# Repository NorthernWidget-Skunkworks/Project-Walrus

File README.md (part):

# The Walrus: A Pressure and Temperature Sensor for Water-Level and Barometric Measurements

***Our Walrus sensor, like this Walrus pup, is equally at home on land or in the water.*** *[Photo by Max Smith](https://commons.wikimedia.org/wiki/File:Walrus_-_Kamogawa_Seaworld_-_pup_-1.jpg)*

## Overview

The **Walrus** is an open-source sensor that measures temperature and pressure. It may be used in the air as a barometer or underwater as part of a system -- combined with barometric compensation -- to obtain changes in water level.

***Hard-mount variant of the Walrus.*** Major components are labeled. The pads to attach the watertight plug for the cable (i.e. the "HardMount"), on left, are currently unpopulated. These may be used for this kind of connector, or may have wires soldered directly to them before being embedded in an epoxy or other potting (i.e., waterproofing and encapsulating) compound.

### Technical specifications

#### Size

Dimensions: 42.0 x 12.7 cm

>> ADD MASS once I get access to a lab balance again <<

#### Operating ranges

**Power**
* Input Voltage: 3.3 to 5.5 V DC
* Logic Voltage: 0 to Vcc (Will operate at same logic level as input power supply)

**Sensors**
* Temperature: -40 to +85 C
* Pressure, typical: 0 to 2 atm (i.e. barometer to 10 m water depth)
* Pressure, maximum, untested: 0 to 30 atm (i.e. barometer to 290 m water depth)
* Cable length: 3 m (I2C) or 1000 m (RS-485).

The pressure operating range depends on the sensor element used. The [**MS5803-02BA**](https://www.te.com/commerce/DocumentDelivery/DDEController?Action=srchrtrv&DocNm=MS5803-02BA&DocType=Data+Sheet&DocLang=English) is the standard model that we use for pressure measurements of up to 10 m

The pressure transducer contains an internal temperature sensor, and a secondary (and more accurate) external temperature sensor is also mounted on the *Walrus*. This external sensor is the [MCP9808](http://www.microchip.com/mymicrochip/filehandler.aspx?ddocname=en556196) in an 8-MSOP package. This sensor has a range of -40 to 125 C.

RS-485 communications allow for a signal to be transmitted over long distances, but require a device that can decode this signal, such as our [Project-Longbow](https://github.com/NorthernWidget-Skunkworks/Project-Longbow).

#### Resolution

Pressure: +/- 1 mm water (0.1 mbar)
Temperature sensor within pressure transducer (typical): +/- 2.0 C
External temperature sensor (typical): +/- 0.5 C

## Circuit board and assembly

The Walrus comes in two forms:
* [Large form factor, through-hole mount](https://github.com/NorthernWidget-Skunkworks/Project-TPDH-Walrus/tree/master/Hardware_LargePTH): This is the legacy board with support for I2C and full-duplex RS-485 communication
* [Smaller form factor, solder pads for wires or a waterproof plug](https://github.com/NorthernWidget-Skunkworks/Project-TPDH-Walrus/tree/master/Hardware_HardMount): This current version makes better use of board space and utilizes a half-duplex RS-485 bus in addition to an I2C bus.

### Files

The files for production are located in folders starting with the word "Hardware". These folders contain:

* "\*.brd" and "\*.sch" files. These are the circuit board and its schematic for use with the EAGLE CAD software, which you can download for free: https://www.autodesk.com/products/eagle/free-download
* A "\*.csv" file that contains the "BoM" -- the bill of materials. This lists all required parts to construct the board
* A ZIP archive containing a set of "Gerber" files. These are the files that machines use to create a circuit board and a stencil to help you to apply solder paste (see below)

### Circuit board specifications

* 2-layer copper
* Minimum trace width: 0.2 mm
* Single-sided
* Surface mount components

All Walrus boards are **single-sided** and use only **surface-mount components** for rapid fabrication using standard equipment.

### Producing circuit boards

We strongly recommend that circuit boards be printed by a reputible manufacturer. Many such industries exist in China, India, and developing or developed countries.

### Populating circuit boards

Before you can start to populate the circuit board, meaning adding components to it, you will need solder paste and a stencil. If you have access to a laser cutter, you can create your own stencil (https://learn.adafruit.com/smt-manufacturing/laser-cut-stencils). If you do not, the company that prints the circuit boards should be able to provide one. If all else fails, you can try to cut out a stencil with a small knife, or use a solder-paste syringe, though both of these methods can lead to difficulties (such as bridged connections). Additional information on how to stencil can be found here: https://www.sparkfun.com/tutorials/58.

To help you in using the stencil, we provide STL files for 3D-printable plates in each of the hardware directories. These plates hold the board in place and provide a level surface on which to use the stencil.

>> ADD PLATE FOR HARDMOUNT <<

After this, you can use a tweezers and steady hands, or a pick-and-place machine, to gently place each component over the right pads, and in the right orientation. Do not worry if they are slightly misaligned; the surface tension of the solderi, once it is melted, will help to rotate the components into place.

### Reflowing circuit boards

"Reflowing" is the process of heating solder until it flows and attaches to components. A basic introduction is here: https://learn.sparkfun.com/tutorials/electronics-assembly/reflow

There are four major ways to reflow:
1. Using a professional oven (see link above)
2. With a customized toaster oven: See https://www.sparkfun.com/tutorials/60, and a basic internet search will show you many, many other ideas
3. You can also use a simple electrical skillet -- the kind that you might use to make some food. https://www.sparkfun.com/tutorials/59
4. Using a hot-air rework station; this is a bit time-intensive, but lets you control the heat, and I often use it for small boards. https://learn.sparkfun.com/tutorials/how-to-use-a-hot-air-rework-station/all

After reflowing, you may need to clean up jumped connections using **solder wick**.

### Debugging circuit boards

After reflow is complete, check if everything worked. Do you have any jumped connections? Any remaining solder paste that hasn't been reflowed? This can be the trickiest part, and one for which access to a multimeter is essential. An oscilloscope and a digital logical analyzer can help too. Debugging electronic circuit boards is a process that requires significant skill and practice, so be sure that you can work with someone with some expertise. I would suggest an electrical engineering student or professor at a local university.

## Wiring and pinout

"Pin" is the name of the pin as labeled on the board. "Wire" is the color of the [Alpha Wire 5004C cable](https://www.digikey.com/product-detail/en/alpha-wire/5004C-SL001/5004CSL001-ND/484976) that we use; you may use something different based on what manufacturers exist where you are; that's okay, just record the color convention! (We sometimes use another cable in which we use a white wire for SDA and a green wire for SCL, but have found that Alpha Wire brand works best.)

>> Add image of cable ends (optional) and find how to integrate with housing section; cabling is a distinct topic, but the step of attaching the cable lies within the housing-construction step <<

### HardMount with plug

Here we assume that you are using standard Alpha Wire cables with waterproof attachments, available in [3-meter](https://www.digikey.com/en/products/detail/alpha-wire/AR0400101-SL357/6555492) and [1-meter](https://www.digikey.com/en/products/detail/alpha-wire/AR0400101-SL356/6555491) lengths; the 3-meter length is our standard because this is the longest that it can be and still communicate reliably via I2C. Because of the wire insulation colors available for these cables and the locations of their attachment points to the [4-pin "HardMount" plug](https://www.digikey.com/product-detail/en/te-connectivity-amp-connectors/1838893-2/A97650-ND/1764165) ([3D model](https://www.traceparts.com/en/product/allied-electronics-automation-m12-panel-mnt-male-4-way?CatalogPath=TRACEPARTS%3ATP09002002001004&Product=10-12012018-106023&PartNumber=1838893-2)), **our HardMount devices do NOT match standard wire-color definitions (or any kind of standard)**. Wire-color definitions are:

| **Color** | **Connection**        |
|-----------|-----------------------|
| Brown     | V+ (3.3-5.5 V)        |
| White     | GND                   |
| Black     | SIG1: SDA or RS-485 A |
| Blue      | SIG2: SCL or RS-485 B |

### Large-form-factor/PTH design: standard wiring suggestion

*These are our more standard wire-color suggestions*

| **Color** | **Connection**                   |
|-----------|----------------------------------|
| Red       | V+ (3.3-5.5 V)                   |
| Black     | GND                              |
| Brown     | SIG1: SDA or RS-485 A (RX+, TX+) |
| Orange    | SIG2: SCL or RS-485 B (RX-, TX-) |

If you attach your own wire, pins on the Walrus are as follows, looking at the top side with the screw hole away from you:
* Top left: SIG1: SDA for I2C; A (+) for RS-485
* Top right: SIG 2: SCL for I2C; B (-) for RS-485
* Bottom left: VCC (3.3V to 5.5V)
* Bottom right: GND

## Upload the firmware

### Downloading and installing the Arduino IDE

Go to https://www.arduino.cc/en/main/software. Choose the proper IDE version for your computer. For Windows, we suggest the non-app version to have more control over Arduino; this might change in the future. You will have to add custom libraries, so the web version will not work (at least, as of the time of writing). Download and install the Arduino IDE. Open it to begin the next steps.

### AVR ISP

To install firmware on the Walrus, you use the [2x3-pin ICSP (also called ISP) header](https://www.digikey.com/product-detail/en/3m/929665-09-03-I/3M156313-06-ND/681796) with a special device called an "in-circuit system programmer" (or just "in-system programmer; yup, that's what the acronym stands for).

Many devices exist to upload firmware, including:
* The official [AVR ISP mkII](http://ww1.microchip.com/downloads/en/DeviceDoc/Atmel-42093-AVR-ISP-mkII_UserGuide.pdf) (no longer produced but available used)
* Using an [Arduino as an ISP](https://www.arduino.cc/en/tutorial/arduinoISP)
* The versatile [Olimex AVR-ISP-MK2](https://www.olimex.com/Products/AVR/Programmers/AVR-ISP-MK2/open-source-hardware)
* The [Adafruit USBtinyISP](https://www.adafruit.com/product/46)

***Note: Be sure to download and/or update drivers for your ISP.***

### Uploading the firmware

Using an AVR ISP, upload the proper firmware programs from the ["Firmware" directory](Firmware) in this repository using the Arduino software:
* Large form factor PTH board
  * I2C mode: No firmware required, but fuses must be set (see instructions, below)
  * RS-485 mode: [Longbow_2BA_0x6B](Firmware/Longbow_2BA_0x6B) (This firmware is for the 02BA; you will need to switch these with other coefficients, available in the commented and uncommented lines of /Firmware/Walrus_I2C_5BA, to modify this for a different transducer pressure range.)
* Small form factor hard-mount board
  * I2C mode: Set the fuses (see instructions below) and then upload [Walrus_I2C_5BA](/Firmware/Walrus_I2C_5BA/) (This firmware is for the 05BA; there are lines in this code to comment and uncomment to modify it for other versions of the Walrus.)
  * RS-485 mode: [Longbow_2BA_0x6B_HalfDuplex](Firmware/Longbow_2BA_0x6B_HalfDuplex) (This firmware is for the 02BA; you will need to switch these with other coefficients, available in the commented and uncommented lines of /Firmware/Walrus_I2C_5BA, to modify this for a different transducer pressure range.)

>> @bschulz1701: could you provide a link to the repo (is it TPDH lib) for "  * I2C mode: No firmware required. Library communicates directly with sensors via their built-in I2C addresses."

**Instructions:**

1. Open the Arduino IDE.
2. Follow [these instructions](https://github.com/SpenceKonde/ATTinyCore/blob/master/Installation.md) to install the [ATTinyCore board definitions](https://github.com/SpenceKonde/ATTinyCore)
3. Select [ATTiny1634](https://github.com/SpenceKonde/ATTinyCore/blob/master/avr/extras/ATtiny_1634.md) **(No bootloader)**
4. Plug your ISP of choice into your computer (via a USB cable) and onto the 6-pin header. There are two ways to place it on; the header is aligned such that the ribbon cable should be facing away from the board while programming. If this fails without being able to upload, try flipping the header around. This should both power the board and provide communications.
5. Go to Tools --> Programmer and select the appropriate programmer based on what you are using.
6. Go to Tools --> Burn Bootloader. Yes, we know that you just selected "ATTiny1634 (No bootloader)", but this step sets the fuses, which configure their internal oscillator and brown-out detection.
7. Unless you are configuring a large-form-factor Walrus in I2C mode (in which case you are now done), open the appropriate firmware (linked above). Then go to Sketch --> Upload Using Programmer. After several seconds, you learn whether you succeeded or failed. Hopefully it worked!

***Uploading using the in-system programmer.***

***Important note for Linux users:*** You must supply permissions to the Arduino IDE for it to be able to use the ICSP, or you will have to run it using `sudo`. The former option is better; the latter is easier in the moment.

## Register map and firmware internals

The Walrus firmware runs on an ATMega microcontroller and exposes an I2C register map to the host logger. The default I2C address is `0x4D`.

Two layouts exist: the **current firmware** (deployed) and the **proposed** layout under [NW-Device-Specification](https://github.com/NorthernWidget/NW-Device-Specification) Schema 1, which the firmware will be updated to implement.

### Current register map (deployed firmware)

26-byte array. Identity fields (MODEL, GROUPID, INDID, FIRMWAREID) mixed into sensor data. Status ready flag is bit 7.

```
0x00        CTRL/Status   bit 7=ready; bits 1:0=update rate selector (0–3)
0x01        —             unused
0x02–0x05   Pressure      int32, µBar (library: val/1000.0 → mBar)
0x06–0x09   Temp ext      int32, 1/10000 °C (MCP9808 external sensor)
0x0A–0x0D   Temp MS5803   int32, 1/10000 °C (MS5803 internal sensor)
0x0E–0x0F   MODEL         uint16 (0x5702)
0x10–0x11   —             gap (nothing loaded)
0x12–0x13   GROUPID       uint16
0x14–0x15   INDID         uint16
0x16–0x17   FIRMWAREID    uint16 (0x0001)
```

### Proposed register map (NW-Device-Specification Schema 1)

Two 32-byte pages. Identity moves entirely to Page 0 (EEPROM). Sensor data in Page 1 (SRAM). No calibration page (MS5803 coefficients are read from its internal PROM at startup).

**Page 0 (0x00–0x1F) — Identity (EEPROM)**

```
Block 0 (0x00–0x07)   Core identity
  0x00        0x01              Schema (NW-Device-Specification v1)
  0x01–0x06   'W','a','l','r','u','s'   Device name (ASCII)
  0x07        0x00              Null padding

Block 1 (0x08–0x0F)   Version
  0x08        HW major
  0x09        HW minor
  0x0A        FW patch          (NW combined-repo convention)
  0x0B–0x0D   0x00,0x00,0x00    Unused (combined repo)
  0x0E–0x0F   0x00,0x00         Reserved

Block 2 (0x10–0x17)   Serial number
  0x10–0x11   0x5702            Board type ('W'=0x57, revision index 2; matches MODEL)
  0x12–0x13   [manufacture]     Group ID
  0x14–0x15   [manufacture]     Unique ID
  0x16–0x17   0x00,0x00         FirmwareID (legacy, reserved)

Block 3 (0x18–0x1F)   Integrity + administration
  0x18–0x1C   0x00 ×5           Reserved
  0x1D        0x00              Magic byte (reserved; purpose TBD)
  0x1E        [computed]        CRC-8 of bytes 0x00–0x1D
  0x1F        0x4D              I2C address (writable; 0xFF = use default)
```

**Page 1 (0x20–0x3F) — Sensor data (SRAM)**

```
Block 0 (0x20–0x27)   MS5803 — pressure + temperature
  0x20        Status       bit 0=ready, bit 1=MS5803 fault, bit 2=ext temp fault
  0x21–0x24   Pressure     int32, µBar, little-endian
  0x25–0x26   Temp MS5803  int16, 0.01 °C, little-endian
  0x27        Reserved

Block 1 (0x28–0x2F)   External temperature sensor (MCP9808)
  0x28–0x29   Temp ext     int16, 0.01 °C, little-endian
  0x2A–0x2F   Reserved

Block 2–3 (0x30–0x3F)   Reserved
```

### Open items before firmware update

Three issues must be resolved before implementing Schema 1:

1. **Status bit:** Current firmware uses bit 7 as the ready flag; Schema 1 uses bit 0. Library `newData()` must be updated to match.
2. **Temperature precision:** Current firmware stores 1/10000 °C (int32, 4 bytes); proposed Schema 1 uses 0.01 °C (int16, 2 bytes). Sensor accuracy (MCP9808 ±0.0625 °C, MS5803 ±1 °C) is well within 0.01 °C resolution.
3. **Pressure units:** Current firmware uses µBar; Haar Schema 1 proposes 0.01 hPa (1 µBar = 0.001 hPa — different units). Resolve unit choice in [NW-Device-Specification](https://github.com/NorthernWidget/NW-Device-Specification) before updating either firmware.

## Housing

### Large-form-factor PTH design

***Walrus v0.0.0 PTH and its housing.*** *Left: 3D-printed top of the housing; the slits are to prevent large material from hitting the sensor. Center: the bottom of the housing. Self-tapping holes are to screw the board onto this housing. The cable entering the housing through a tightly-fitting hole on the "south" side of the image has not yet been stripped to expose the ends of the individual wires. A different variant of the housing is longer to allow the user to strip more of the cable if desired while maintaining the cable jacketing in contact with the hole. Top right: Walrus v0.0.0. This fully-functional initial version is significantly larger than the current unit. Note the pressure transducer (white circle) at top left, and the fact that this has pins and hardware for a full-duplex RS-485 connection. Bottom right: U.S. penny for scale; 19.05 mm (0.75 inch) diameter.*

### HardMount design

***Render of the enclosure design.*** *The epoxy encapsulation tray sits within a wider cylinder containing a screen designed to keep sediment out. Design still in progress (19 June 2020).*

### How to build

#### Materials and components required

##### All models

* 3D printer filament: ABS suggested
* Two-part epoxy: [3M DP270 Clear](https://multimedia.3m.com/mws/media/66773O/3mtm-scotch-weldtm-epoxy-potting-compound-adhesive-dp270.pdf); can be purchased from [McMaster-Carr](https://www.mcmaster.com/7467A274)
* Conformal coating to help protect components during epoxy encapsulation. We suggest [MG 419D](https://www.mgchemicals.com/products/conformal-coatings/acrylic-conformal-coating-419d) ([Digi-Key purchase link](https://www.digikey.com/product-detail/en/mg-chemicals/419D-55ML/473-1388-ND)). If you prefer a silicone conformal coat, we suggest [MG 422C](https://www.mgchemicals.com/products/conformal-coatings/422c-silicone-conformal-coating), though we recommend this instead for an external (rather than internal, as this will be), flexible coat.

##### HardMount with Plug

* [4-pin "HardMount" plug](https://www.digikey.com/product-detail/en/te-connectivity-amp-connectors/1838893-2/A97650-ND/1764165) ([3D model](https://www.traceparts.com/en/product/allied-electronics-automation-m12-panel-mnt-male-4-way?CatalogPath=TRACEPARTS%3ATP09002002001004&Product=10-12012018-106023&PartNumber=1838893-2))
* HardMount cable: **Alpha Wire AR0400105-SL357** (-40 PVC jacket)
  * [Alpha Wire page](http://www.Alpha Wire.com/en/Products/Connectivity/AlphaConnect/Cordsets/AR0400105)
  * [Example from DigiKey](https://www.digikey.com/product-detail/en/alpha-wire/AR0400105-SL357/AR0400105SL357-ND/6555497)
  * Comes in a [variety of lengths from 0.6 to 20 meters](http://www.Alpha Wire.com/en/Products/Connectivity/AlphaConnect/Cordsets/AR0400105) ([Digi-Key search results](https://www.digikey.com/products/en/cable-assemblies/circular-cable-assemblies/448?FV=2331%7C312745%2C2344%7C346572%2C2350%7C349292%2C2380%7C203167%2C-8%7C448%2C2345%7C1%2C2352%7C387800&quantity=0&ColumnSort=77&page=1&stock=1&rohs=1&nstock=1&k=M12+Alpha+Wire&pageSize=25&pkeyword=M12+Alpha+Wire))
  * User may choose a cable that terminates in a plug, alongside a matching recepticle in the wall of the data-logger box, for a specialized solution that does not require cable glands.
* One [#2-56 x 3/16" thread-cutting screw](https://www.fastenal.com/products/details/0143391) per board to fasten it to the housing for the epoxy encapsulation

##### PTH or "HardMount" design without plug

* 7x [\#4-24 self-tapping screws](https://www.polycase.com/screws-mbr-100) ([Additional link: untested but probably identical screw from Fastenal](https://www.fastenal.com/products/details/32244))
  * 3x to hold board in place
  * 4x to to attach the lid of the 3D-printed enclosure

*Assuming that we are using a 4-wire connection instead of the full-bridge RS-485 (supported by the large-form-factor/PTH board) because this is being phased out in favor of a 4-wire half-bridge.*

* [4-conductor Alpha Wire](https://www.digikey.com/product-detail/en/alpha-wire/5004C-SL001/5004CSL001-ND/484976), soldered to pads or rings

#### 3D printing the housing

Subfolders of the "3Dprint" directory contain "STL" files that you can use with a program called "[Slic3r](https://slic3r.org/)" to create 3-D printable parts for your housing. Assuming that you have a Prusa 3D printer, you will want to download the [Prusa variant of Slic3r](https://www.prusa3d.com/prusaslicer/). This comes with the appropriate setup files and information to help you configure the printer and print your parts.

>> Link to all housings once designed <<

>> TO DO: Options for HardMount with (and perhaps without) the plug. <<

#### Cabling

##### HardMount with Plug

Solder the HardMount plug onto the four SMD pads with the notch (for plug orientation) at the bottom side of the board. The best way to do this is to:
* Add small pillows of solder to each of the four pads, enough to create contact with the HardMount solder cups but not so much that it is not possible to slide the HardMount plug over them.
* Slide the HardMount plug on; it will take a bit of finesse to keep it from being pushed off of the solder pillows.
* Using some Blu Tack (or equivalent), fix the board and HardMount plug in place
* Double-check that the notch in the HardMount plug is on the back side of the board
* Solder on the first connection
* Check whether the board is straight; reflow the solder as needed until the connection is secure
* Solder the second connection
* Flip the board, ensuring that it is straight (if not, make changes)
* Solder the other two solder-cup connections

##### PTH or "HardMount" design without plug

Optionally, pass the cable through its hole in the 3D-printed enclosure bottom for the pour-over epoxy encapsulation. This means that you will not later need to pass the full length of the cable through the hole!

Next, solder the cable through the rings or onto the SMD pads. Ensure that all connections are solid prior to encapsulation. The encapsulation process will strain-relieve the cable.

#### Potting

>> @bschulz1701: with this epoxy, do we need to conformally coat the boards first?

After creating the housing, affix the logger to it using the \#4-24 screws listed above. If the design includes an integrated cable (instead of a HardMount plug), MAKE SURE that a cable of the desired length is attached beforehand! Otherwise, MAKE SURE that a HardMount plug is attached beforehand!

>> @superchap123: Your clip design would come in here too.

Before applying the epoxy, make sure that all zones where epoxy could leak out of the 3D-printed lower portion of the enclosure are sealed. The epoxy is somewhat viscous, so gaps need not be made completely airtight.

Next, pot the boards in 2-part epoxy (per the supplies list above, we suggest [3M DP270 Clear](https://multimedia.3m.com/mws/media/66773O/3mtm-scotch-weldtm-epoxy-potting-compound-adhesive-dp270.pdf); can be purchased from [McMaster-Carr](https://www.mcmaster.com/7467A274)). Be careful to fully cover everything except for the white inside membrane on the pressure transducer. If epoxy touches this, it is rendered unreliable or useless.

>> Walk through assembly with images <<

***Potting the large-form-factor Walrus.*** *3D print designs for this lower/tray portion and the to-be-attached lid are included [within this repository in the "3Dprint" folder](https://github.com/NorthernWidget-Skunkworks/Project-Walrus/tree/master/3Dprint/HousingLargePTH).*

## Wiring to logger

These instructions assume that you are using a [Margay](https://github.com/NorthernWidget-Skunkworks/Project-Margay) or [Okapi](https://github.com/NorthernWidget-Skunkworks/Project-Okapi) data logger. If this is not the case, similar pins are available on a generic Arduino board.

### HardMount Plug

Pass the cable through the housing to the logger, ideally using a cable gland that you can tighten on the box containing the logger: this can provide waterproofing as well as some strain relief. Follow the table in the [Wiring and pinout](#Wiring-and-pinout) section to attach individual wires to the appropriate pins on the data logger and (if needed) RS-485 converter. In bulleted-list form, with colors given for [Alpha Wire 5004C](https://www.digikey.com/product-detail/en/alpha-wire/5004C-SL001/5004CSL001-ND/484976):

### Power

* V- (Walrus) to GND or V- (Logger)
* V+ (Walrus) to a positive voltage source between 3.3 and 5.5 V (Logger)

#### I2C

If using the sensor in I2C mode, attach the signal wires as follows:
* SIG1 (Walrus) to SDA (Logger)
* SIG2 (Walrus) to SCL (Logger)

#### RS-485

If using the sensor in RS-485 mode, attach the signal wires to the Longbow Backpack as follows:
* SIG1 (Walrus) to A+ (Longbow)
* SIG2 (Walrus) to B- (Longbow)
(You may use another RS-485 converter, in which case the wiring is up to you!)

**Then use another set of four wires to connect the Longbow to the logger:**
* GND to GND
* Vin to a 3.3 to 5.5 V power source
* SDA to SDA
* SCL to SCL
We recommend [Pololu's pre-crimped wires](https://www.pololu.com/category/71/wires-with-pre-crimped-terminals) for this with a male terminal, as it ensures that you can have these four wires in the proper order for both the Walrus and the data logger. For this reason, Northern Widget data loggers ([Margay](https://github.com/NorthernWidget-Skunkworks/Project-Margay) and [Okapi](https://github.com/NorthernWidget-Skunkworks/Project-Okapi)) always have these four pins in the order:
* GND
* V+
* SDA
* SCL

## Writing a program to connect to the Walrus sensor

After uploading the Walrus firmware, you should be able to use any standard Arduino device to connect to it and read its data.

The firmware uploaded to the Arduino device should include the [Walrus library](https://github.com/NorthernWidget-Skunkworks/Walrus_Library) as demonstrated below. Documentation for the Walrus library, auto-generated using doxygen, is available on its linked GitHub page.

### Very simple Arduino code

#### I2C

This code is intended for any generic Arduino system.

>> Note: Not all of this code is built yet. THIS IS A TEMPLATE!

```c++
// Include the Walrus library
#include "Walrus_I2C.h"

// Declare variables -- just as strings
String header;
String data;

// Instantiate class
Walrus myWalrus;

void setup(){
    // Begin Serial connection to computer at 38400 baud
    Serial.begin(38400);
    // Obtain the header just once
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
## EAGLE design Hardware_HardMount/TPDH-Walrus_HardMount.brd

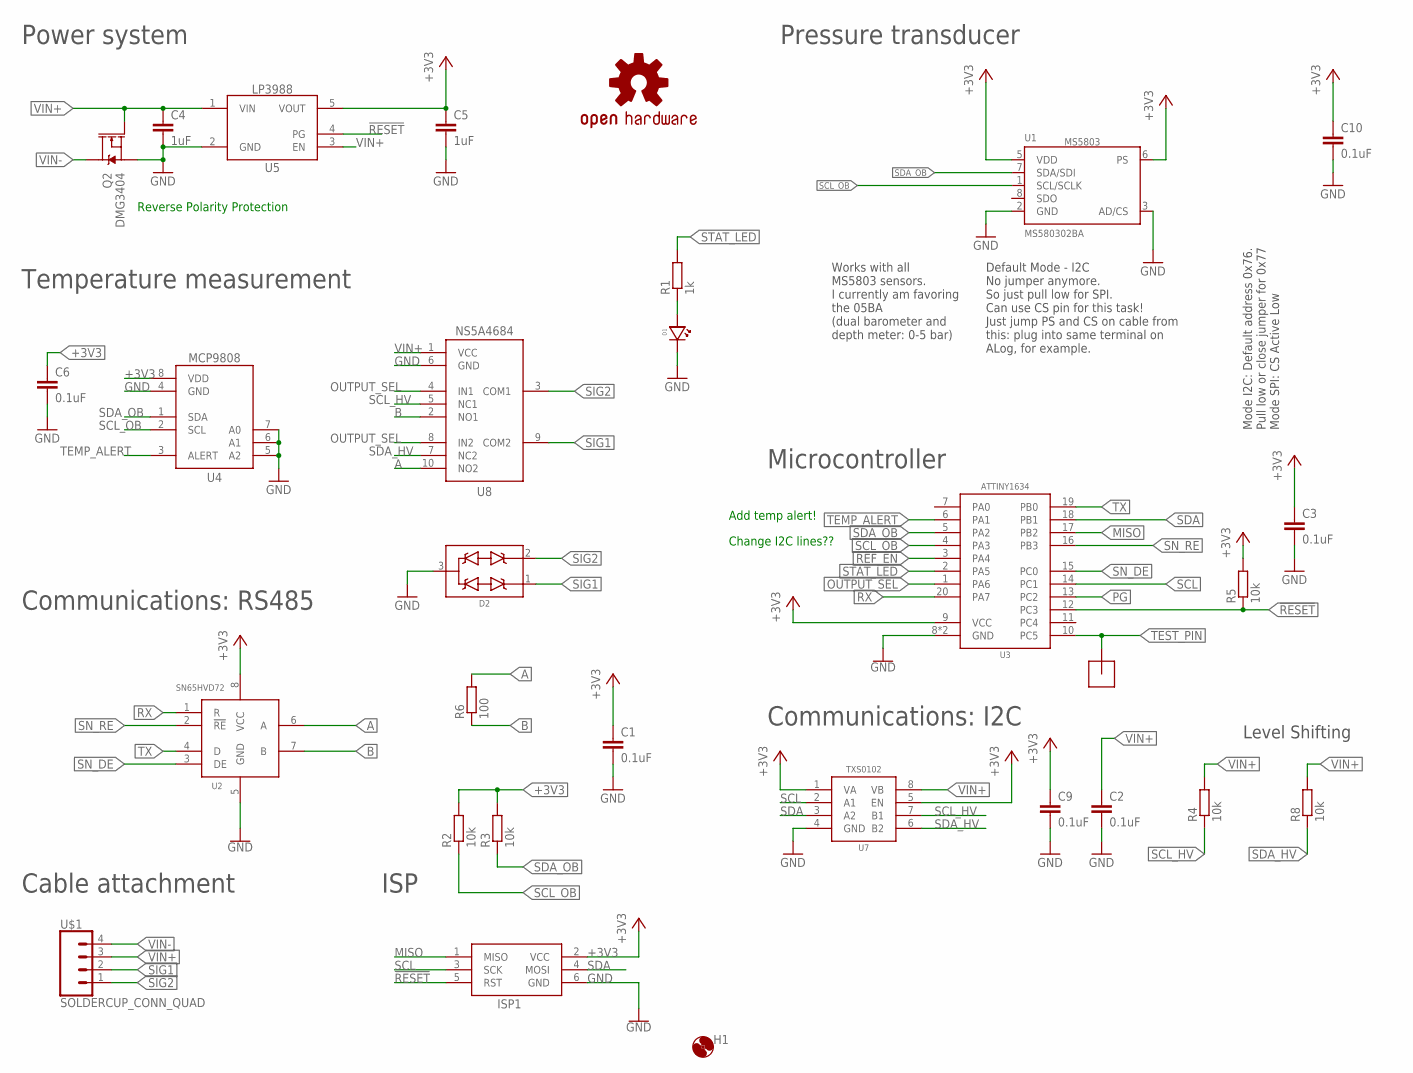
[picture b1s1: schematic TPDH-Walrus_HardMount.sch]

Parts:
C1, C2, C3, C6, C9, C10: 0.1uF; C0402
C4, C5: 1uF; C0603
D1: LEDBLUE0603; LED_0603
D2: TVSSM712; SOT23-3
H1: MOUNTING_HOLE2_NP; 2_56
ISP1: AVRISP-6; AVRISP
LOGO1: OSHW-LOGOM; OSHW-LOGO-M
Q2: DMG3404; SOT23-3
R1: 1k; R0603
R2, R3, R4, R5, R8: 10k; R0402
R6: 100; R0402
U1: MS580302BA; MS5803
U2: SN65HVD72DSOIC; SO08
U3: ATTINY1634QFN; QFN20
U4: MCP9808MSOP; MSOP_8
U5: LP39883.3VDBV; DBV0005A
U7: TXS0102DQM; DQM_R-PX2SON-N8
U8: NS5A4684S; WQFN10
U$1: SOLDERCUP_CONN_QUAD
U$12: POGO_PAD

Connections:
!RESET: ISP1.5 (RST), R5.1, U3.12 (PC3), U5.4 (PG)
+3V3: C1.1, C3.1, C5.1, C6.1, C9.1, C10.1, ISP1.2 (VCC), R2.2, R3.2, R5.2, U1.5 (VDD), U1.6 (PS), U2.8 (VCC), U3.9 (VCC), U4.8 (VDD), U5.5 (VOUT), U7.1 (VA), U7.5 (EN)
A: R6.2, U2.6 (A), U8.10 (NO2)
B: R6.1, U2.7 (B), U8.2 (NO1)
GND: C1.2, C2.2, C3.2, C4.2, C5.2, C6.2, C9.2, C10.2, D1.CATHODE, D2.3 (COM), ISP1.6 (GND), Q2.2 (S), U1.2 (GND), U1.3 (AD/CS), U2.5 (GND), U3.8 (GND), U3.EP (GND), U4.4 (GND), U4.5 (A2), U4.6 (A1), U4.7 (A0), U5.2 (GND), U7.4 (GND), U8.6 (GND)
MISO: ISP1.1 (MISO), U3.17 (PB2)
unnamed: D1.ANODE, R1.1
OUTPUT_SEL: U3.1 (PA6), U8.4 (IN1), U8.8 (IN2)
PG: U3.13 (PC2)
REF_EN: U3.3 (PA4)
RX: U2.1 (R), U3.20 (PA7)
SCL: ISP1.3 (SCK), U3.14 (PC1), U7.2 (A1)
SCL_HV: R4.1, U7.7 (B1), U8.5 (NC1)
SCL_OB: R2.1, U1.1 (SCL/SCLK), U3.4 (PA3), U4.2 (SCL)
SDA: ISP1.4 (MOSI), U3.18 (PB1), U7.3 (A2)
SDA_HV: R8.1, U7.6 (B2), U8.7 (NC2)
SDA_OB: R3.1, U1.7 (SDA/SDI), U3.5 (PA2), U4.1 (SDA)
SIG1: D2.1 (D1), U8.9 (COM2), U$1.2
SIG2: D2.2 (D2), U8.3 (COM1), U$1.1
SN_DE: U2.3 (DE), U3.15 (PC0)
SN_RE: U2.2 (!RE), U3.16 (PB3)
STAT_LED: R1.2, U3.2 (PA5)
TEMP_ALERT: U3.6 (PA1), U4.3 (ALERT)
TEST_PIN: U3.10 (PC5), U$12.P$1
TX: U2.4 (D), U3.19 (PB0)
VIN+: C2.1, C4.1, Q2.1 (G), R4.2, R8.2, U5.1 (VIN), U5.3 (EN), U7.8 (VB), U8.1 (VCC), U$1.3
VIN-: Q2.3 (D), U$1.4

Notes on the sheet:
Default Mode - I2C No jumper anymore. So just pull low for SPI. Can use CS pin for this task! Just jump PS and CS on cable from this: plug into same terminal on ALog, for example.
Mode I2C: Default address 0x76. Pull low or close jumper for 0x77 Mode SPI: CS Active Low
Works with all MS5803 sensors. I currently am favoring the 05BA (dual barometer and depth meter: 0-5 bar)
Reverse Polarity Protection
Level Shifting
Pressure transducer
Cable attachment
Communications: I2C
ISP
Communications: RS485
Temperature measurement
Power system
Microcontroller
Change I2C lines??
Add temp alert!

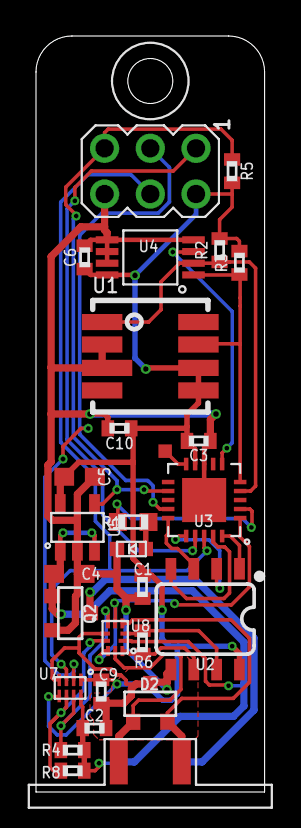
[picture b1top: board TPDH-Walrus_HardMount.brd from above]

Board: 2 copper layers, 12.7 x 42.0 mm, 30 parts (1 on the bottom side), 25 nets.

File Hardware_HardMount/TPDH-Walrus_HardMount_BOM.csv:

"Qty","Value","Device","Package","Parts","Description","DIGIKEY","DISP","MF","MPN","PROD_ID","VALUE","VALUE_PART",
"1","","ATTINY1634QFN","QFN20","U3","ATtiny1634 8 bit AVR Microcontroller","ATTINY1634-MURCT-ND","","Atmel","ATTINY1634-MUR","","","",
"1","","MOUNTING_HOLE2_NP","2_56","H1","Genaric Mechanical Mounting Hole","DNP","","N/A","DNP","","","",
"1","","TVSSM712","SOT23-3","D2","Generic dual channel TVS diode","CDSOT23-SM712CT-ND","","Bourns","CDSOT23-SM712","","","",
"6","0.1uF","C-EU0.1UFC0402","C0402","C1, C2, C3, C6, C9, C10","CAPACITOR, European symbol","490-4759-1-ND","","Murata","GCM155R71C104KA55D","","","",
"1","100","R-EU_100R0402","R0402","R6","RESISTOR, European symbol","311-100LRCT-ND","","Yageo","RC0402FR-07100RL","","","100",
"5","10k","R-EU_10KR0402","R0402","R2, R3, R4, R5, R8","RESISTOR, European symbol","311-10.0KLRCT-ND","","Yageo","RC0402FR-0710KL","","","10k",
"1","1k","R-EU_1KR0603","R0603","R1","RESISTOR, European symbol","311-1KLDCT-ND","","Yageo","AC0603FR-071KL","","","1k",
"2","1uF","C-EU1UFC0603","C0603","C4, C5","CAPACITOR, European symbol","1276-6524-1-ND","","Samsung","1276-6524-1-ND","","","",
"1","AVRISP-6","AVRISP-6","AVRISP","ISP1","AVR ISP HEADER","","","","","","","",
"1","DMG3404","MOSFET-NCH-DMG3404L","SOT23-3","Q2","N-channel MOSFETs","DMG3404L-7DICT-ND","","Diodes Incorporated","DMG3404L-7","","DMG3404","",
"1","LEDBLUE0603","LEDBLUE0603","LED_0603","D1","Genaric LED","732-4966-1-ND","","Wurth","150060BS75000","","","",
"1","LP39883.3VDBV","LP39883.3VDBV","DBV0005A","U5","TPS7A05* - Ultra Low Power Ultra Low Dropout Linear Regulator with Power Good","LP3988IMF-3.3/NOPBCT-ND","","TI","LP3988IMF-3.3/NOPB","","","",
"1","MCP9808MSOP","MCP9808MSOP","MSOP_8","U4","MCP9808 - Digital Temperature Sensor","MCP9808T-E/MSCT-ND","","Microchip","MCP9808T-E/MS","","","",
"1","MS580302BA","MS580302BA","MS5803","U1","MS5803 - Minature Media Compatible Pressure Sensor","223-1624-5-ND","","TE Connectivity","MS580302BA01-00","","","",
"1","NS5A4684S","NS5A4684S","WQFN10","U8","NS5A4684S - Dual Analog Multiplexer (1:2)","NS5A4684SMNTAGOSCT-ND","NS5A4684","ON Semiconductor","NS5A4684SMNTAG","","","",
"1","OSHW-LOGOM","OSHW-LOGOM","OSHW-LOGO-M","LOGO1","Open-Source Hardware (OSHW) Logo","DNP","","N/A","DNP","","","",
"1","POGO_PAD","POGO_PAD","POGO_PAD","U$12","POGO Pad","DNP","","N/A","DNP","","","",
"1","SN65HVD72DSOIC","SN65HVD72DSOIC","SO08","U2","SN65HVD72 - Half Duplex RS-485 Tranciver, with output enable","296-39179-1-ND","SN65HVD72","TI","SN65HVD72DR","","","",
"1","SOLDERCUP_CONN_QUAD","SOLDERCUP_CONN_QUAD","SOLDERCUP_CONN_QUAD","U$1","Mounting pads for a M12 barel connector","A97650-ND","","TE Connectivity","1838893-2","","","",
"1","TXS0102DQM","TXS0102DQM","DQM_R-PX2SON-N8","U7","TXS0102 - 2 Channel Bidirectional Voltage Level Translator","296-28435-1-ND","","TI","TXS0102DQMR","","","",

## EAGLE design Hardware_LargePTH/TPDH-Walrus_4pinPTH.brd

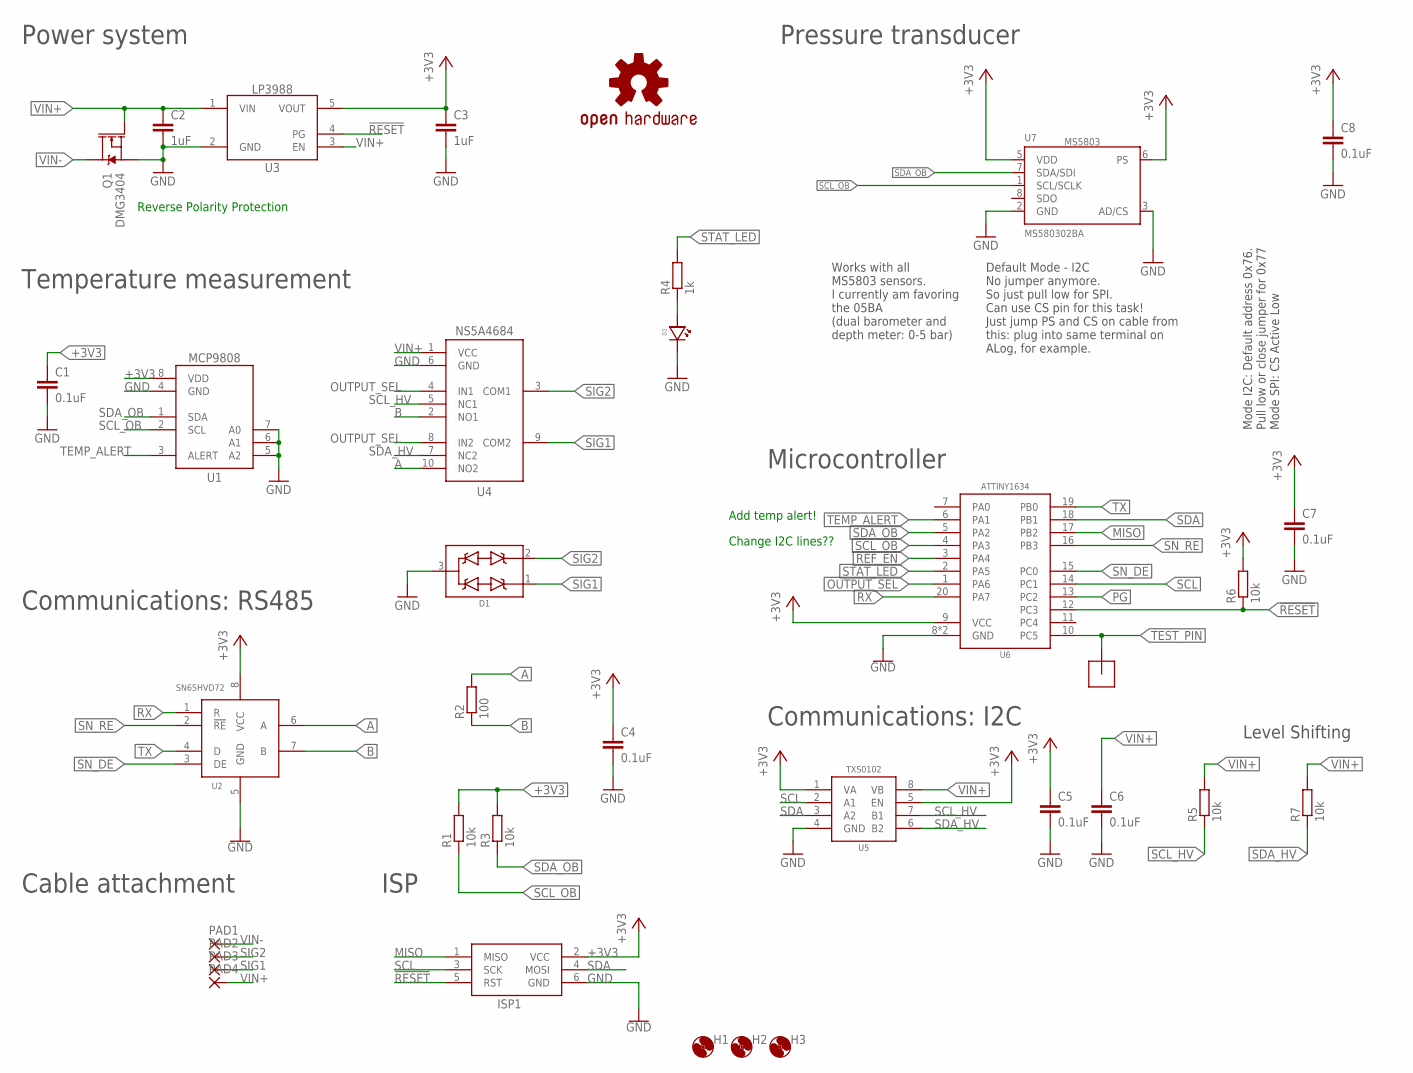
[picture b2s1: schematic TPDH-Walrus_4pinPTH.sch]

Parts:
C1, C4, C5, C6, C7, C8: 0.1uF; C0402
C2, C3: 1uF; C0603
D1: TVSSM712; SOT23-3
D2: LEDBLUE0603; LED_0603
H1, H2, H3: MOUNTING_HOLE2_NP; 2_56
ISP1: AVRISP-6; AVRISP
LOGO1: OSHW-LOGOM; OSHW-LOGO-M
PAD1, PAD2, PAD3, PAD4: PAD1.1MM; 2,54/1,1
Q1: DMG3404; SOT23-3
R1, R3, R5, R6, R7: 10k; R0402
R2: 100; R0402
R4: 1k; R0603
TP1: POGO_PAD
U1: MCP9808MSOP; MSOP_8
U2: SN65HVD72DSOIC; SO08
U3: LP39883.3VDBV; DBV0005A
U4: NS5A4684S; WQFN10
U5: TXS0102DQM; DQM_R-PX2SON-N8
U6: ATTINY1634QFN; QFN20
U7: MS580302BA; MS5803; MPN MS580305BA01-00; DIGIKEY 223-1625-5-ND

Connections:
!RESET: ISP1.5 (RST), R6.1, U3.4 (PG), U6.12 (PC3)
+3V3: C1.1, C3.1, C4.1, C5.1, C7.1, C8.1, ISP1.2 (VCC), R1.2, R3.2, R6.2, U1.8 (VDD), U2.8 (VCC), U3.5 (VOUT), U5.1 (VA), U5.5 (EN), U6.9 (VCC), U7.5 (VDD), U7.6 (PS)
A: R2.2, U2.6 (A), U4.10 (NO2)
B: R2.1, U2.7 (B), U4.2 (NO1)
GND: C1.2, C2.2, C3.2, C4.2, C5.2, C6.2, C7.2, C8.2, D1.3 (COM), D2.CATHODE, ISP1.6 (GND), Q1.2 (S), U1.4 (GND), U1.5 (A2), U1.6 (A1), U1.7 (A0), U2.5 (GND), U3.2 (GND), U4.6 (GND), U5.4 (GND), U6.8 (GND), U6.EP (GND), U7.2 (GND), U7.3 (AD/CS)
MISO: ISP1.1 (MISO), U6.17 (PB2)
unnamed: D2.ANODE, R4.1
OUTPUT_SEL: U4.4 (IN1), U4.8 (IN2), U6.1 (PA6)
PG: U6.13 (PC2)
REF_EN: U6.3 (PA4)
RX: U2.1 (R), U6.20 (PA7)
SCL: ISP1.3 (SCK), U5.2 (A1), U6.14 (PC1)
SCL_HV: R5.1, U4.5 (NC1), U5.7 (B1)
SCL_OB: R1.1, U1.2 (SCL), U6.4 (PA3), U7.1 (SCL/SCLK)
SDA: ISP1.4 (MOSI), U5.3 (A2), U6.18 (PB1)
SDA_HV: R7.1, U4.7 (NC2), U5.6 (B2)
SDA_OB: R3.1, U1.1 (SDA), U6.5 (PA2), U7.7 (SDA/SDI)
SIG1: D1.1 (D1), PAD3.1, U4.9 (COM2)
SIG2: D1.2 (D2), PAD2.1, U4.3 (COM1)
SN_DE: U2.3 (DE), U6.15 (PC0)
SN_RE: U2.2 (!RE), U6.16 (PB3)
STAT_LED: R4.2, U6.2 (PA5)
TEMP_ALERT: U1.3 (ALERT), U6.6 (PA1)
TEST_PIN: TP1.P$1, U6.10 (PC5)
TX: U2.4 (D), U6.19 (PB0)
VIN+: C2.1, C6.1, PAD4.1, Q1.1 (G), R5.2, R7.2, U3.1 (VIN), U3.3 (EN), U4.1 (VCC), U5.8 (VB)
VIN-: PAD1.1, Q1.3 (D)

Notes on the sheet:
Default Mode - I2C No jumper anymore. So just pull low for SPI. Can use CS pin for this task! Just jump PS and CS on cable from this: plug into same terminal on ALog, for example.
Mode I2C: Default address 0x76. Pull low or close jumper for 0x77 Mode SPI: CS Active Low
Works with all MS5803 sensors. I currently am favoring the 05BA (dual barometer and depth meter: 0-5 bar)
Reverse Polarity Protection
Level Shifting
Pressure transducer
Cable attachment
Communications: I2C
ISP
Communications: RS485
Temperature measurement
Power system
Microcontroller
Change I2C lines??
Add temp alert!

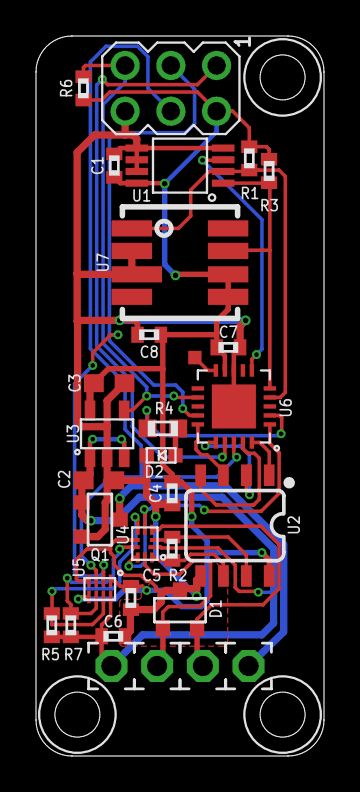
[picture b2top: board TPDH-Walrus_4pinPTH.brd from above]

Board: 2 copper layers, 16.0 x 40.0 mm, 35 parts (1 on the bottom side), 25 nets.

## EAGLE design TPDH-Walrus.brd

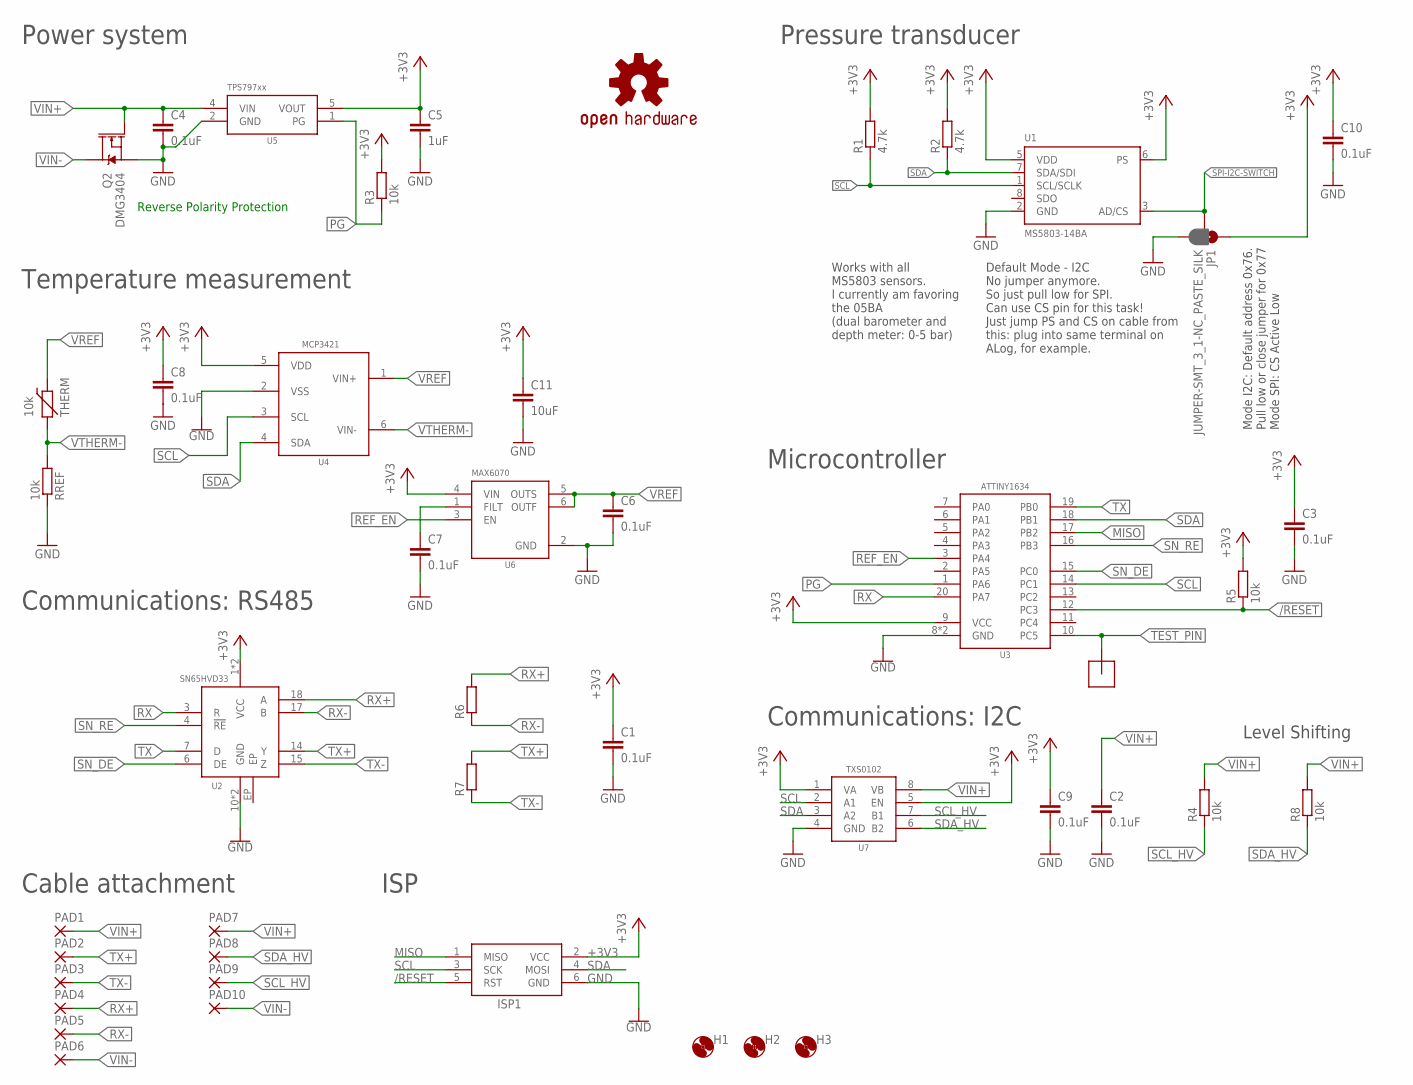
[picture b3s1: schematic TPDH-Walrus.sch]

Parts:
C1, C2, C3, C4, C6, C7, C8, C9, C10: 0.1uF; C0402
C5: 1uF; C0603
C11: 10uF; C0805
H1, H2, H3: MOUNTING_HOLE2_NP; 2_56
ISP1: AVRISP-6; AVRISP
JP1: JUMPER-SMT_3_1-NC_PASTE_SILK; SMT-JUMPER_3_1-NC_PASTE_SILK
LOGO1: OSHW-LOGOM; OSHW-LOGO-M
PAD1, PAD2, PAD3, PAD4, PAD5, PAD6, PAD7, PAD8, PAD9, PAD10: 2,15/1,0
Q2: DMG3404; SOT23-3
R1, R2: 4.7k; R0402
R3, R4, R5, R8: 10k; R0402
R6, R7: R-EU_100R0402; R0402
RREF: 10k; R0603; MPN ERA-3AEB103V; DIGIKEY P10KDBCT-ND
THERM: 10k; R0603
U1: MS5803-14BA; MS5803; MPN MS580305BA01-00; DIGIKEY 223-1625-5-ND
U2: SN65HVD33RHL; VQFN-20_POWER
U3: ATTINY1634QFN; QFN20
U4: MCP3421A3; SOT23-6L
U5: TPS79733; DCK_R-PDSO-G5
U6: MAX6070AAUT18; SOT23-6L
U7: TXS0102DQM; DQM_R-PX2SON-N8
U$12: POGO_PAD

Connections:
+3V3: C1.1, C3.1, C5.1, C8.1, C9.1, C10.1, C11.1, ISP1.2 (VCC), JP1.1, R1.2, R2.2, R3.2, R5.2, U1.5 (VDD), U1.6 (PS), U2.1 (VCC), U2.20 (VCC), U3.9 (VCC), U4.5 (VDD), U5.5 (VOUT), U6.4 (VIN), U7.1 (VA), U7.5 (EN)
/RESET: ISP1.5 (RST), R5.1, U3.12 (PC3)
GND: C1.2, C2.2, C3.2, C4.2, C5.2, C6.2, C7.2, C8.2, C9.2, C10.2, C11.2, ISP1.6 (GND), JP1.3, Q2.2 (S), RREF.1, U1.2 (GND), U2.10 (GND), U2.11 (GND), U3.8 (GND), U3.EP (GND), U4.2 (VSS), U5.2 (GND), U6.2 (GND), U7.4 (GND)
MISO: ISP1.1 (MISO), U3.17 (PB2)
unnamed: C7.1, U6.1 (FILT)
PG: R3.1, U3.1 (PA6), U5.1 (PG)
REF_EN: U3.3 (PA4), U6.3 (EN)
RX: U2.3 (R), U3.20 (PA7)
RX+: PAD4.1, R6.2, U2.18 (A)
RX-: PAD5.1, R6.1, U2.17 (B)
SCL: ISP1.3 (SCK), R1.1, U1.1 (SCL/SCLK), U3.14 (PC1), U4.3 (SCL), U7.2 (A1)
SCL_HV: PAD9.1, R4.1, U7.7 (B1)
SDA: ISP1.4 (MOSI), R2.1, U1.7 (SDA/SDI), U3.18 (PB1), U4.4 (SDA), U7.3 (A2)
SDA_HV: PAD8.1, R8.1, U7.6 (B2)
SN_DE: U2.6 (DE), U3.15 (PC0)
SN_RE: U2.4 (!RE), U3.16 (PB3)
SPI-I2C-SWITCH: JP1.2, U1.3 (AD/CS)
TEST_PIN: U3.10 (PC5), U$12.P$1
TX: U2.7 (D), U3.19 (PB0)
TX+: PAD2.1, R7.2, U2.14 (Y)
TX-: PAD3.1, R7.1, U2.15 (Z)
VIN+: C2.1, C4.1, PAD1.1, PAD7.1, Q2.1 (G), R4.2, R8.2, U5.4 (VIN), U7.8 (VB)
VIN-: PAD6.1, PAD10.1, Q2.3 (D)
VREF: C6.1, THERM.1 (2), U4.1 (VIN+), U6.5 (OUTS), U6.6 (OUTF)
VTHERM-: RREF.2, THERM.2 (1), U4.6 (VIN-)

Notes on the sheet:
Default Mode - I2C No jumper anymore. So just pull low for SPI. Can use CS pin for this task! Just jump PS and CS on cable from this: plug into same terminal on ALog, for example.
Mode I2C: Default address 0x76. Pull low or close jumper for 0x77 Mode SPI: CS Active Low
Works with all MS5803 sensors. I currently am favoring the 05BA (dual barometer and depth meter: 0-5 bar)
Reverse Polarity Protection
Level Shifting
Pressure transducer
Cable attachment
Communications: I2C
ISP
Communications: RS485
Temperature measurement
Power system
Microcontroller

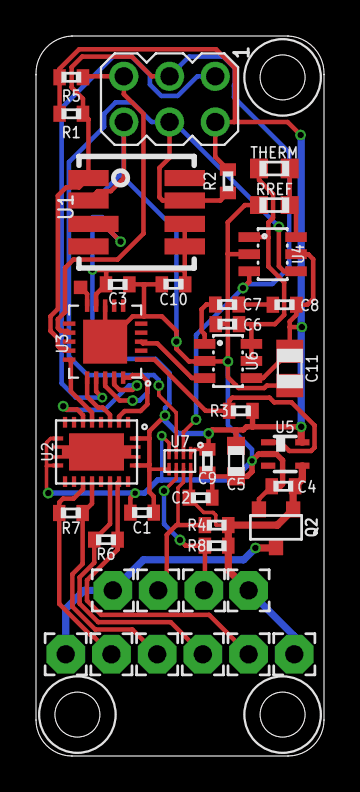
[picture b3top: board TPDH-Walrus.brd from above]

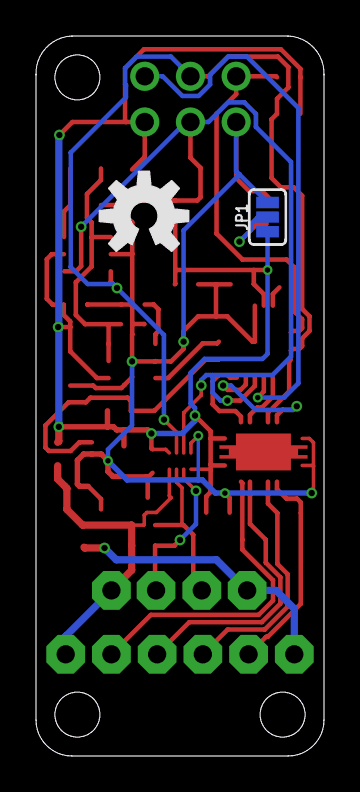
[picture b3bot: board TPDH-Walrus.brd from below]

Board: 2 copper layers, 16.0 x 40.0 mm, 46 parts (2 on the bottom side), 25 nets.

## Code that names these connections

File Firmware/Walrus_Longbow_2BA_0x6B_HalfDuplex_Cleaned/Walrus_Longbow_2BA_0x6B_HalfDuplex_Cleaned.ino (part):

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#define EOF ']'

// Pins for ATTiny1634
#define SN_DE 13
#define SN_RE 14
#define REF_EN 4

uint16_t coefficient[8];// Coefficients;

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  	Serial.begin(4800);

  	// For ATTiny 1634 -- aka Walrus
  	pinMode(SN_DE, OUTPUT);
  	pinMode(SN_RE, OUTPUT);
  	pinMode(REF_EN, OUTPUT);

    // Begin in minion mode by default, recieve on, transmit off
  	digitalWrite(SN_DE, LOW);
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
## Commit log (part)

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2018-10-27 License CC-BY-SA-4
2018-10-27 Larger board, mid-route * QFN packages * ISP header * solder holes for the cable * Hand-routed * Most pogo pads removed
2018-10-27 PTH ISP, more routing
2018-10-31 multiple schematic and layout updates * status indicator * LDO reset * move thermistor by power supply and voltage reference * rip up traces and reorganize
2018-10-31 ATTiny1634 on schematic
2018-10-31 Level shifter on schematic
2018-10-31 Connected level shifter, added passives
    Added schematic connections for level shifter, also added decoupling capacitors and relabeled IC values
2018-11-01 all components approx placed
2018-11-02 Routed
2018-11-02 Update +3V3 symbol and re-route
2018-11-02 1 via, lots of work
2018-11-03 Name SPI-I2C switch
2018-11-03 Cable solder ring silk
2018-11-03 Preparation for organization
2018-11-03 First schematic organization
2018-11-05 Minor fixes for DRC
    Changed power path very slightly, also changed to 0.2mm traces for TSX0102 to avoid clearance issues
2018-11-05 Major revision Add 10 uF cap Reroute to keep decoupling caps near ICs Change schematic to reflect the above reorganization Reroute to move thermistor to upper right
2018-11-05 Vin complete
2018-11-06 Thermistor passives placed
2018-11-06 Thermistor ICs
2018-11-06 mostly routed
2018-11-06 add SDO for I2C
2018-11-06 Routed, DRC passed
2018-11-06 Partial ERC
2018-11-06 Partial ERC approval
2018-11-06 Fixed thermistor divider, removed SDO
    Changed thermistor voltage to VRef rather than 3v3, and removed connection to SDO pin.
2018-11-07 Therm: reconnect and rearrange
2018-11-07 power pad update; uniform board outline
2018-11-07 Update clearance, wire access; reroute
2018-11-07 top and bottom cable silk
2018-11-07 I2C silk - DEFAULT: 0x77, ALT: 0x76
2018-11-07 Improved power layout, minor edits
    Improved the overall layout of the power (3v3 and GND) as well as a few other minor edits. Changed orientation of I2C pins to match previous designs, also made pad on SN65HVD33 floating
2018-11-08 Clean up routing, clear DRC stubs
2018-11-08 Approve ERC: no value for pad, holes
2018-11-27 Gerbers
2018-12-17 Silk placement and OSH logo
2018-12-17 OSH Park Gerbers
2018-12-24 Updated silk for production
2019-01-02 Standardized naming
2019-01-04 Minor silk screen updates, generated gerbers
    Minor silk screen updates for v0.0.0 before submitting to fab, generated gerbers and sent to fab
2019-01-16 ATTiny1634 name bschulz.lbr
2019-01-19 Added first Gen1 housing
    Added solidworks and STL file for first generation of housing
2019-01-25 ATTiny1634 compatible
2019-01-25 Fixed syntax error in firmware
2019-02-02 Updated firmware to support `Wire.h`
    Changed firmware to use most well supported (and much faster!) Wire hardware library, now that we no longer need to use a software implementation due to memory constriction
2019-04-21 CC BY-SA 4.0 International: official wording
2019-07-08 Updates to BOM info and silkscreen
2019-07-08 Initial hardmount variant
    Start of hard mount variant design, several design update choices required
2019-07-08 Added half duplex firmware variant
    Tested for functionality, works, needs more extensive testing
2019-07-10 Updated silkscreen on Walrus v0.0
2019-07-10 Initial layout for Hard mount (v0.1) variant, cleanup required
2019-07-11 Continued layout, final cleanup required
    Cleanup and pours required
2019-07-15 Minor layout updates, sent to fab
    Cleaned up layout, sent to fab
2019-08-03 Added BOM for hard mount, minor part number cleanup
2019-08-13 Update to v0.1 hardware, review required
    Initial update complete, requires review and verification of various fixes
2019-08-13 Board cleanup, final DFM for v0.2, added gerbers
2019-09-25 Added hole dimension callouts to Walrus v1
    Added callouts to board file and added separate picture for easy reference
2019-09-25 Added preliminary design for v2 alternative mounting
    Added a v2 design with mounting pattern which is compatible with the v1 Walrus and no removable connector
2019-09-26 Minor updates and cleanup, sent v2 NoConn to fab
    Minor silkscreen and trace cleanup, sent v2 of through hole variant out to fab
2020-02-20 Generated updated BoM
    Updated BoM to fix R1 part value
2020-02-28 Updated readme info with pinout, etc
2020-04-25 HardMount directory
2020-04-25 Remove ZIP archives: manage with releases in future
2020-04-25 Original PTH and enclosure to its folder
2020-04-25 4-pin version in Hardware_LargePTH
2020-04-25 Proper attribution to Schulz
2020-04-25 Dimension information with STL
2020-04-25 Renumbering script can live in repo history
2020-04-25 Wrong text! Commercial OK.
2020-04-25 Return key ZIP files for manufacturing with descriptive names
2020-04-27 Basic instructions
2020-04-27 Added MS5803 Calculations document
    Added rendered PDF, raw Latex, and included logo for rendering
2020-04-28 Images, figures, and more assembly/component information
2020-04-28 No filename spaces; images to documentation folder
2020-04-28 Stenciling board-mount plate
2020-04-28 Stencil mount plate, cabling notes
2020-04-30 Move housings into 3Dprint folder
2020-04-30 Screw-in housing for conformal-coated board
2020-04-30 even surface for stenciling solder paste
2020-04-30 New 3D print location
2020-04-30 CC BY-SA 4.0
2020-04-30 GPL for code
2020-05-07 More detailed instructions
2020-05-07 Updated part numbers and BoM for HardMount variant
    Updated part numbers in BoM to specifically indicate DNP where appropriate and to change MS5803 PN to 2BA model instead of 5BA model
2020-05-24 connections: not included in BoM CSV (board only)
2020-05-25 Cabling
2020-05-25 Cabling + parts list links
2020-05-25 Epoxy P/N and links; ABS filament
2020-05-25 Standard and tall ICSP; rm cable for non-HardMount
2020-05-25 Cable to sensor; ICSP header options
2020-05-25 ICSP header standard height DigiKey link
2020-05-25 Firmware upload: detailed instructions
2020-05-25 I2C firmware
2020-06-01 AlphaWire cable specs and links
2020-06-01 Assembly and cabling
2020-06-02 Direct AlphaWire link for lengths (0.6 to 20 m)
2020-06-18 Template for Arduino library
2020-06-18 Acknowledgments: UMN and WMO
2020-06-18 rm whitespace
2020-06-18 Remove blank line between images
2020-06-19 Rev A (captured screw, captured pipe screen)
    Rev A Walrus potting mold and sensor housing
2020-06-19 Remove temp files
2020-06-19 HardMount epoxy-pour plate and enclosure render from @superchap123
2020-07-02 Indicate that Longbow (RS-485) firmware is for Walrus
2020-07-04 Half-duplex firmware, edited for readability
2020-07-04 *.swp
2020-07-21 Set fuses + firmware
2020-08-02 I2C+Margay instructions
2020-08-05 Added Walrus I2C Firmware - ALPHA
    Added Walrus I2C firmware for 5BA board, very dirty, but functionality is there, needs further testing
2020-08-06 I2C firmware scaling updates
    Changed the scaling of the variables to ensure no loss of resolution
2020-08-06 Fixed negative values for MCP9808
    Fixed math error which caused incorrect values for MCP9808 (`TempDH`) temp readout
2020-08-06 0x4D default; Symbiont -> Walrus
2020-08-06 Ohhhhhhh.... VCC and GND power colors flipped!
2020-08-06 1 more Symbiont -> Walrus in comments
2020-08-07 Removed startup delay on Walrus firmware
    Removed 500ms delay on startup, erroneous debugging step
2020-08-07 Update I2C firmware to make sure temp sensor has good value
    Make sure to wait 250ms before grabbing data from temp sensor (maximum sample time required)
2020-08-08 Alpha Wire and HardMount plug connections
2020-08-08 HardMount plug soldering instructions
2020-08-08 "Bootloader" for fuses: Oscillator + brown-out detection
2020-08-08 Update numbering after noting bootloader for fuses
2020-08-08 Bootloader typo
2020-08-08 Epoxy encapsulation example: large form factor
2020-08-08 Move to git LFS
2020-08-10 Input range 3.3V to 5.5V
2020-09-08 updateMeasurements() is now subsumed into getString()
2020-09-10 Housing uses screw; acts as stilling well
2020-09-10 Screws; conformal coat
2020-09-10 Note silicone conformal coat option
2021-02-13 Missing files that constitute the assembly
2021-02-13 Cylindrical housing for conformally coated (only) board
2021-02-13 Newest housing with epoxy-fill tray and external enclosure designed by @superchap123
2021-02-13 Firmware for Arduino logger device: note and link
2021-02-13 I2C link and note about transducer pressure ranges
2021-03-02 DOI badge
2021-07-18 run/margay logger example code fix
2021-07-19 ISP driver note
2021-07-19 shift resnik to okapi
2021-07-22 small spelling change
2021-07-23 quote changes
2021-08-08 note consistency changes
2021-09-08 HardMount-terminated cables
2026-06-02 Add CITATION.cff and .zenodo.json for v0.3.0 release
2026-06-02 README: switch DOI badge to concept DOI
2026-06-02 CITATION.cff: add abstract and keywords
2026-06-02 Revert "Firmware: flip ready flag from bit 7 to bit 0 (Schema 1)"
    This reverts commit 7fc8bd6b5a46fda533f78a189a5199bab5478194.
2026-06-02 Firmware: migrate default I2C address 0x4D → 0x57 (Schema 1 'W' mnemonic)
2026-06-02 Firmware: remove dead ADR_Alt (0x41 now reserved for Apis)

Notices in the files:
README.md:
This work is licensed under a Creative Commons Attribution-ShareAlike 4.0 International License.
parts and their libraries:
SparkFun-Aesthetics: Licensing: Creative Commons ShareAlike 4.0 International - https://creativecommons.org/licenses/by-sa/4.0
bschulz: This work is licensed under the Creative Commons Attribution-ShareAlike 4.0
http://creativecommons.org/licenses/by-sa/4.0
